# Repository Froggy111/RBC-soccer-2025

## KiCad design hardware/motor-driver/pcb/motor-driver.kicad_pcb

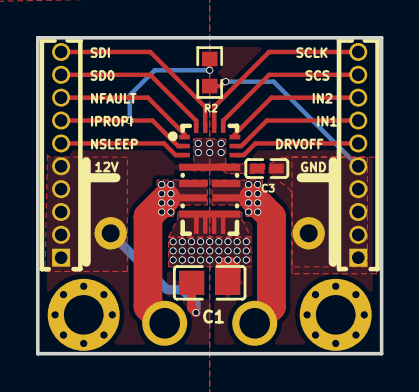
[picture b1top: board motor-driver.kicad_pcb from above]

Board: 2 copper layers, 19.1 x 17.6 mm, 9 parts (1 on the bottom side), 14 nets.

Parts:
C1: 22uF; C0805
C3: 100nF; C0402
DRV8244: DRV8244SQRYJRQ1; VQFN-16_L6.0-W3.0-P0.50-TL
M2_1, M2_2: M2
R2: 680Ω; R0603
U1: XT30PW-F; CONN-TH_XT30PW-F-1
U2, U3: X1311WV-10J-C40D24; HDR-TH_10P-P1.27-V-M

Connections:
12V: C1.1, C3.1, DRV8244.4, U1.4, U3.1, U3.2, U3.3, U3.4, U3.5
DRVOFF: DRV8244.10, U2.6
GND: C1.2, C3.2, DRV8244.7, R2.2, U1.3, U2.1, U2.2, U2.3, U2.4, U2.5
IN1: DRV8244.11, U2.7
IN2: DRV8244.12, U2.8
IPROPI: DRV8244.2, R2.1, U3.7
NFAULT: DRV8244.1, U3.8
NSLEEP: DRV8244.3, U3.6
OUT1: DRV8244.8, DRV8244.9, U1.2
OUT2: DRV8244.5, DRV8244.6, U1.1
SCLK: DRV8244.14, U2.10
SCS: DRV8244.13, U2.9
SDI: DRV8244.15, U3.10
SDO: DRV8244.16, U3.9

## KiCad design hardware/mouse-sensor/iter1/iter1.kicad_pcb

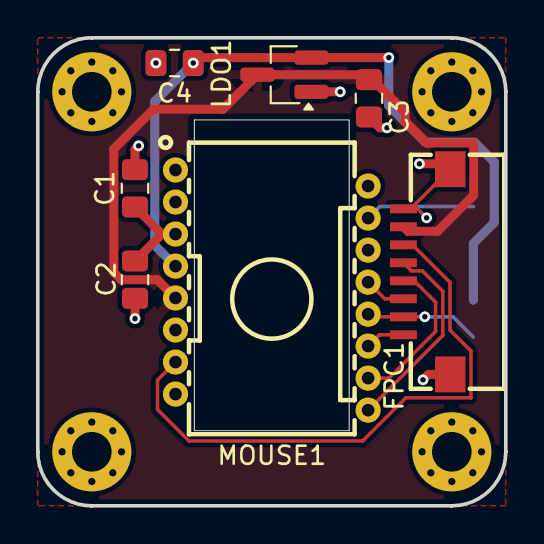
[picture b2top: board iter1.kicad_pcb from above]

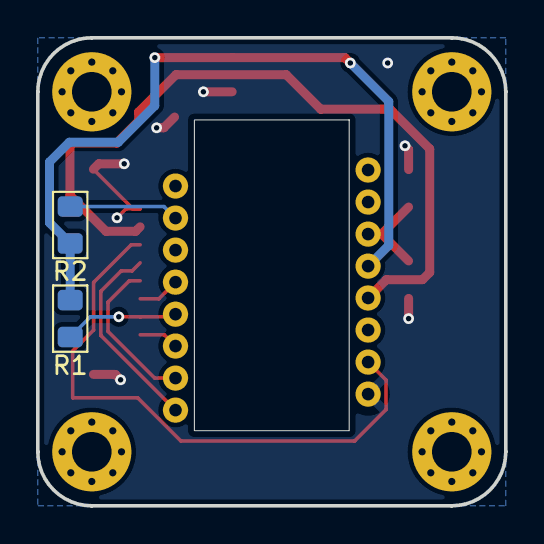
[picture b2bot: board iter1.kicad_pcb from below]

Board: 2 copper layers, 26.0 x 26.0 mm, 13 parts (2 on the bottom side), 11 nets.

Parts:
C1: 100nF; C_0805_2012Metric_Pad1.18x1.45mm_HandSolder
C2: 4.7uF; C_0805_2012Metric_Pad1.18x1.45mm_HandSolder
C3, C4: 1u; C_0805_2012Metric_Pad1.18x1.45mm_HandSolder
FPC1: FC10-S08FCT-00; FPC-SMD_8P-P1.00_DEALON_FC10-S08FCT-00
H1, H2, H3, H4: M2; MountingHole_2.2mm_M2_Pad_Via
LDO1: XC6206P182MR-MS; SOT-23_Handsoldering
MOUSE1: PMW3360DM-T2QU; PDIP-16_L16.2-W9.1-P1.78-TL_PMW3389DM-T3QU
R1: 10k; R_0805_2012Metric_Pad1.15x1.40mm_HandSolder
R2: 39; R_0805_2012Metric_Pad1.15x1.40mm_HandSolder

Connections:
+1V8: C4.1, LDO1.2 (VOUT), MOUSE1.4 (VDD), R1.2, R2.1
+3V3: C3.1, FPC1.7, LDO1.3 (VIN), MOUSE1.5 (VDDIO)
/MISO: FPC1.2, MOUSE1.12 (MISO), R1.1
/MOSI: FPC1.1, MOUSE1.11 (MOSI)
/MOT: FPC1.5, MOUSE1.9 (MOTION)
/RST: FPC1.6, MOUSE1.7 (NRESET)
/SCLK: FPC1.4, MOUSE1.10 (SCLK)
/SCS: FPC1.3, MOUSE1.13 (NCS)
GND: C1.2, C2.2, C3.2, C4.2, FPC1.8, FPC1.9, FPC1.10, LDO1.1 (VSS), MOUSE1.8 (GND)
unnamed: MOUSE1.15 (LED_P), R2.2
unnamed: C1.1, C2.1, MOUSE1.3 (VDDPIX)

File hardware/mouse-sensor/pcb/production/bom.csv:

Designator,Footprint,Quantity,Value,LCSC Part #
C1,0805,1,100nF,
C2,0805,1,4.7uF,
"C3, C4",0805,2,1u,
FPC1,FPC-SMD_8P-P1.00_DEALON_FC10-S08FCT-00,1,FC10-S08FCT-00,C2998898
LDO1,SOT-23_Handsoldering,1,XC6206P182MR-MS,C5252894
MOUSE1,PDIP-16_L16.2-W9.1-P1.78-TL_PMW3389DM-T3QU,1,PMW3360DM-T2QU,C20612443
R1,0805,1,10k,
R2,0805,1,39,

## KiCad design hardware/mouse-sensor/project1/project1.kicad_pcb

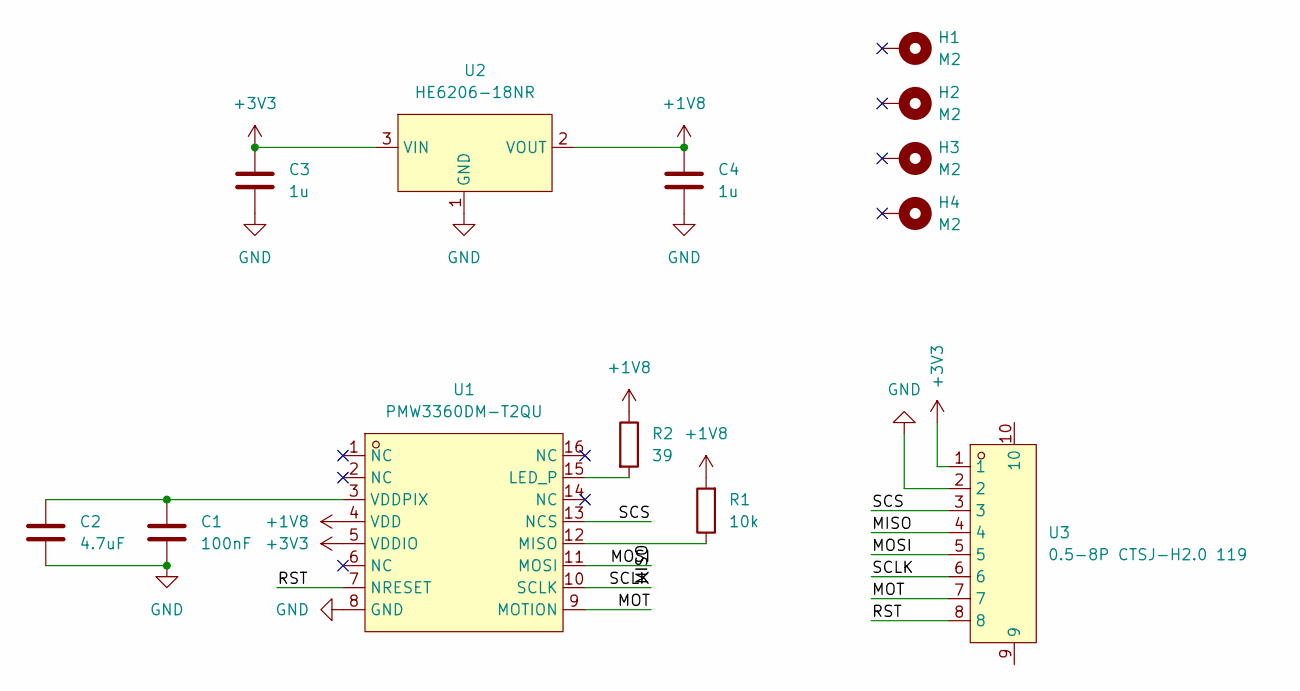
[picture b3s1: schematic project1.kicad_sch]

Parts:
C1: 100nF; C_0805_2012Metric_Pad1.18x1.45mm_HandSolder
C2: 4.7uF; C_0805_2012Metric_Pad1.18x1.45mm_HandSolder
C3, C4: 1u; C_0805_2012Metric_Pad1.18x1.45mm_HandSolder
H1, H2, H3, H4: M2; MountingHole_2.2mm_M2_Pad_Via
R1: 10k; R_0603_1608Metric_Pad1.05x0.95mm
R2: 39; R_0603_1608Metric_Pad1.05x0.95mm
U1: PMW3360DM-T2QU; PDIP-16_L16.2-W9.1-P1.78-TL_PMW3389DM-T3QU; LCSC Part C20612443
U2: HE6206-18NR; SOT-23_BigPads; LCSC Part C5199437
U3: 0.5-8P CTSJ-H2.0 119; FPC-SMD_8P-P0.50_SHOUHAN_CTSJ-H2.0; LCSC Part C5373445

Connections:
+1V8: C4.1, R1.2, R2.1, U1.4 (VDD), U2.2 (VOUT)
+3V3: C3.1, U1.5 (VDDIO), U2.3 (VIN), U3.1
/MISO: R1.1, U1.12 (MISO), U3.4
/MOSI: U1.11 (MOSI), U3.5
/MOT: U1.9 (MOTION), U3.7
/RST: U1.7 (NRESET), U3.8
/SCLK: U1.10 (SCLK), U3.6
/SCS: U1.13 (NCS), U3.3
GND: C1.2, C2.2, C3.2, C4.2, U1.8 (GND), U2.1 (GND), U3.2
unnamed: R2.2, U1.15 (LED_P)
unnamed: C1.1, C2.1, U1.3 (VDDPIX)

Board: 2 copper layers, 13 parts (0 on the bottom side), 11 nets, no tracks yet.
